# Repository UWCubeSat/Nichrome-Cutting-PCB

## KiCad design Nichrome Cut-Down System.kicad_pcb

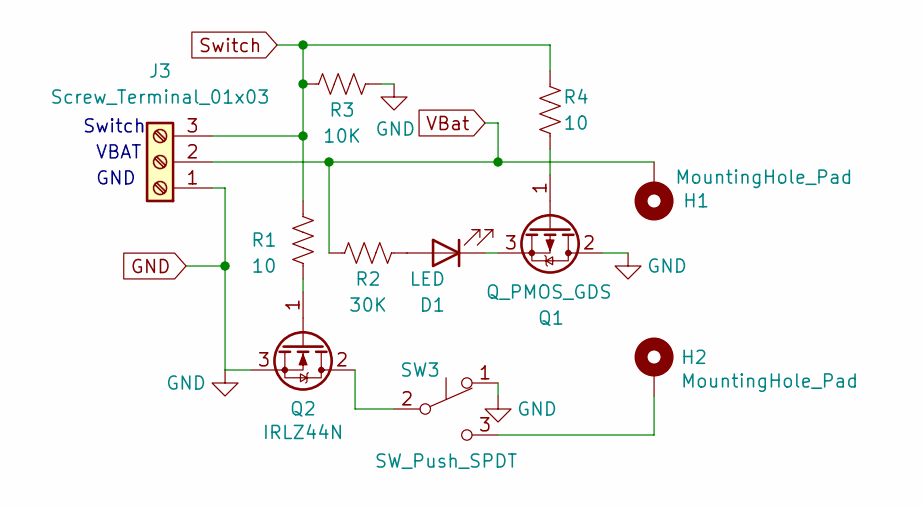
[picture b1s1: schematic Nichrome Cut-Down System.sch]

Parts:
D1: LED; LED_D5.0mm_FlatTop
H1, H2: MountingHole_Pad; MountingHole_2.5mm_Pad_TopBottom
J3: Screw_Terminal_01x03; TerminalBlock_Phoenix_PT-1,5-3-5.0-H_1x03_P5.00mm_Horizontal
Q1: Q_PMOS_GDS; P-Channel_MOSFET_TO-251A
Q2: IRLZ44N; TO-220-3_Horizontal_TabDown
R1, R4: 10; R_Axial_DIN0204_L3.6mm_D1.6mm_P5.08mm_Horizontal
R2: 30K; R_Axial_DIN0204_L3.6mm_D1.6mm_P5.08mm_Horizontal
R3: 10K; R_Axial_DIN0204_L3.6mm_D1.6mm_P5.08mm_Horizontal
SW3: SW_Push_SPDT; Limit_Switch_JL012-13.5-2

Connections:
GND: J3.1, Q1.2 (D), Q2.3 (S), R3.2, SW3.1 (A)
unnamed: D1.1 (K), Q1.3 (S)
unnamed: D1.2 (A), R2.2
unnamed: H2.1, SW3.3 (C)
unnamed: Q1.1 (G), R4.1
unnamed: Q2.1 (G), R1.2
unnamed: Q2.2 (D), SW3.2 (B)
Switch: J3.3, R1.1, R3.1, R4.2
VBat: H1.1, J3.2, R2.1

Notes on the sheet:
Switch
VBAT
GND

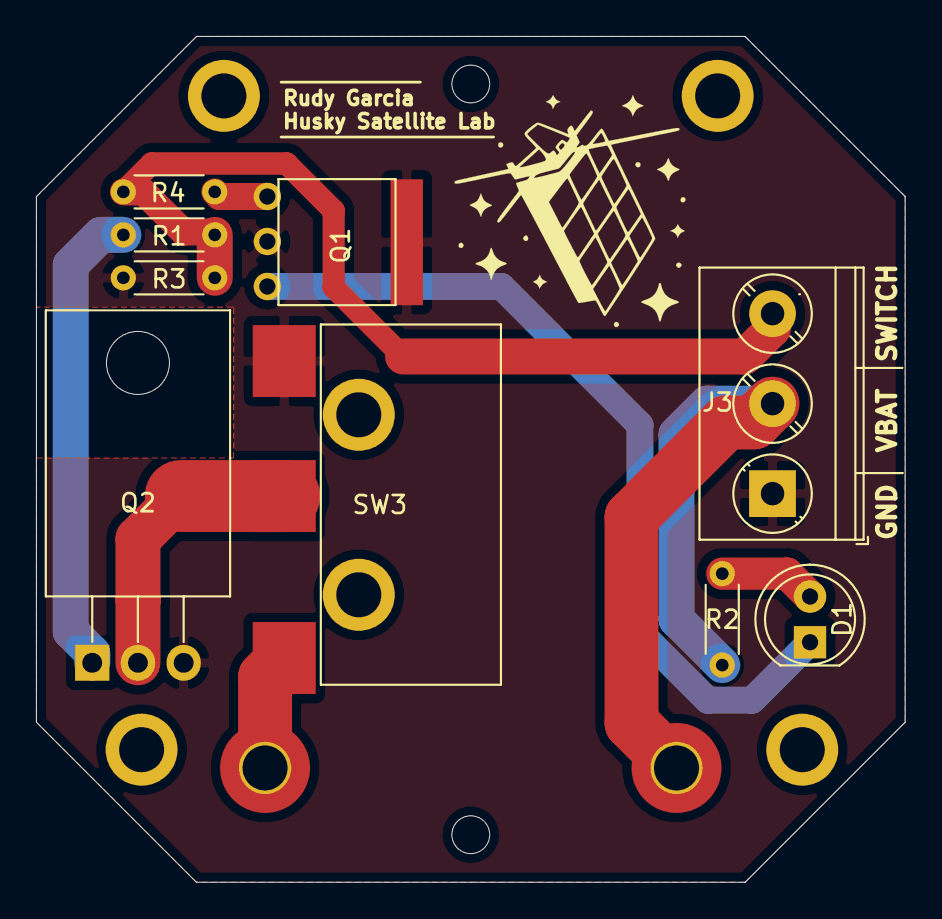
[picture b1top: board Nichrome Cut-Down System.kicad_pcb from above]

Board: 2 copper layers, 48.3 x 47.0 mm, 11 parts (0 on the bottom side), 9 nets.

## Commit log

2022-01-24 KiCAD
    KiCAD Documents for Review
2022-02-15 Design Review Changes Implemented
    Changed diamond shaped holes to circular shaped holes for fishing line and reducing potential issues with JLCPCB. Also removed MOSFET tab surface mount pad to reduce potential issues with JLCPCB orde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
